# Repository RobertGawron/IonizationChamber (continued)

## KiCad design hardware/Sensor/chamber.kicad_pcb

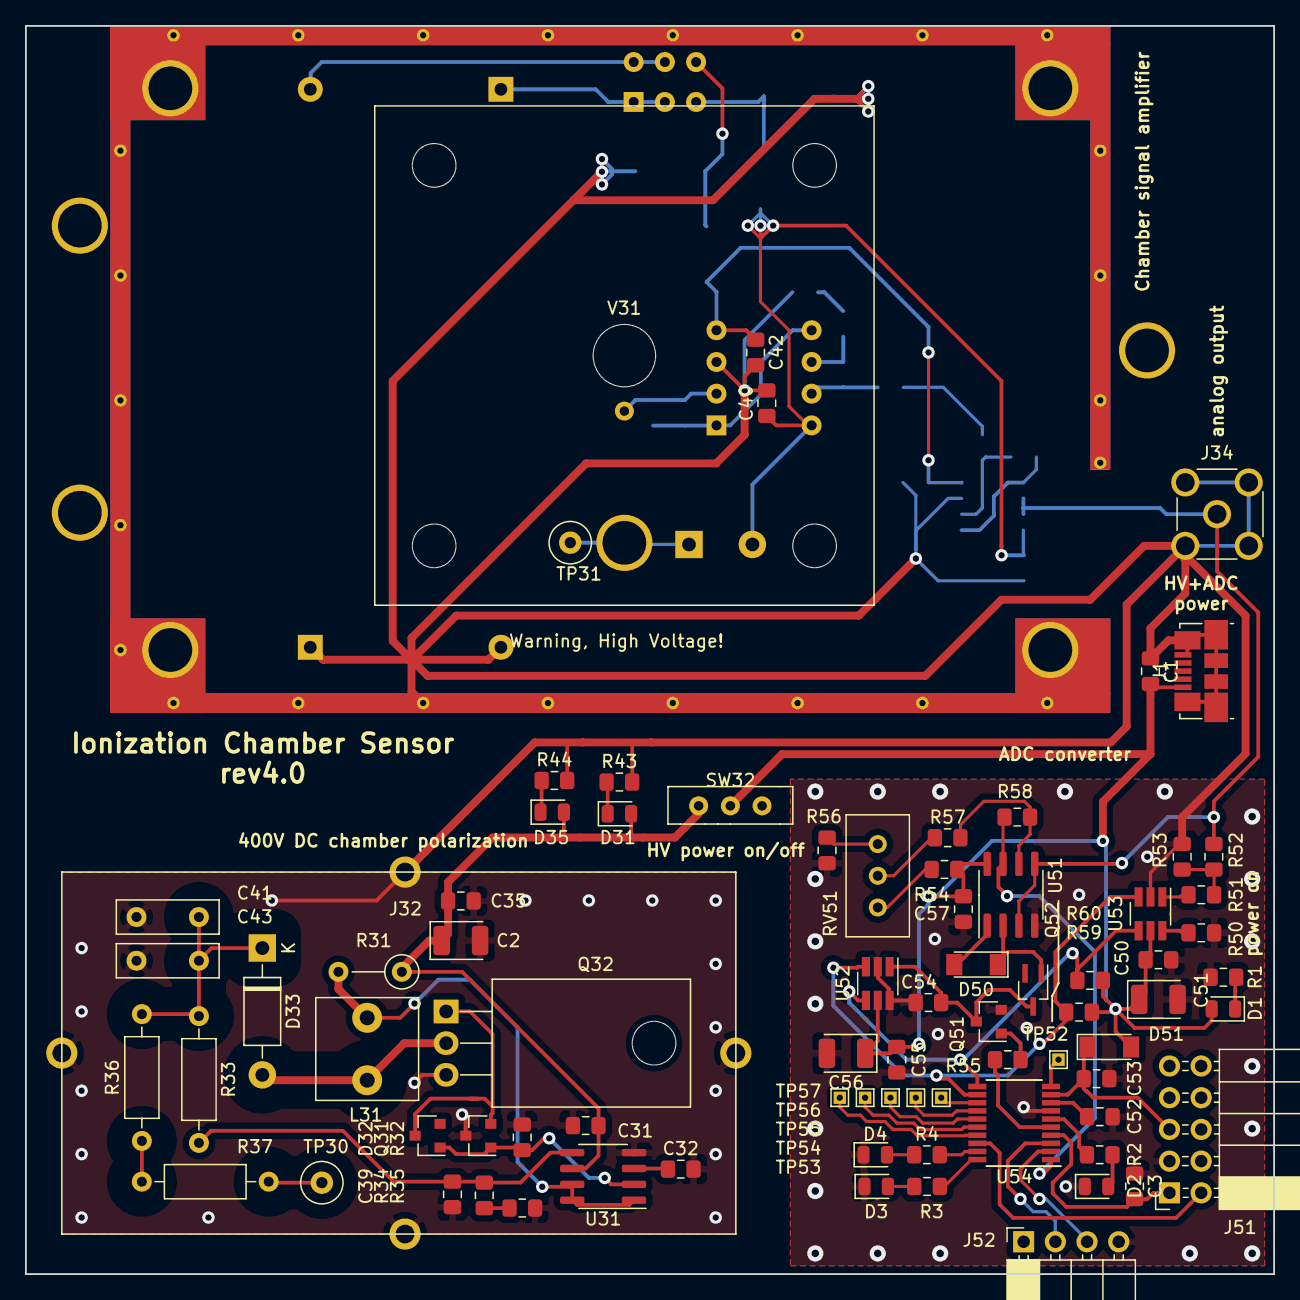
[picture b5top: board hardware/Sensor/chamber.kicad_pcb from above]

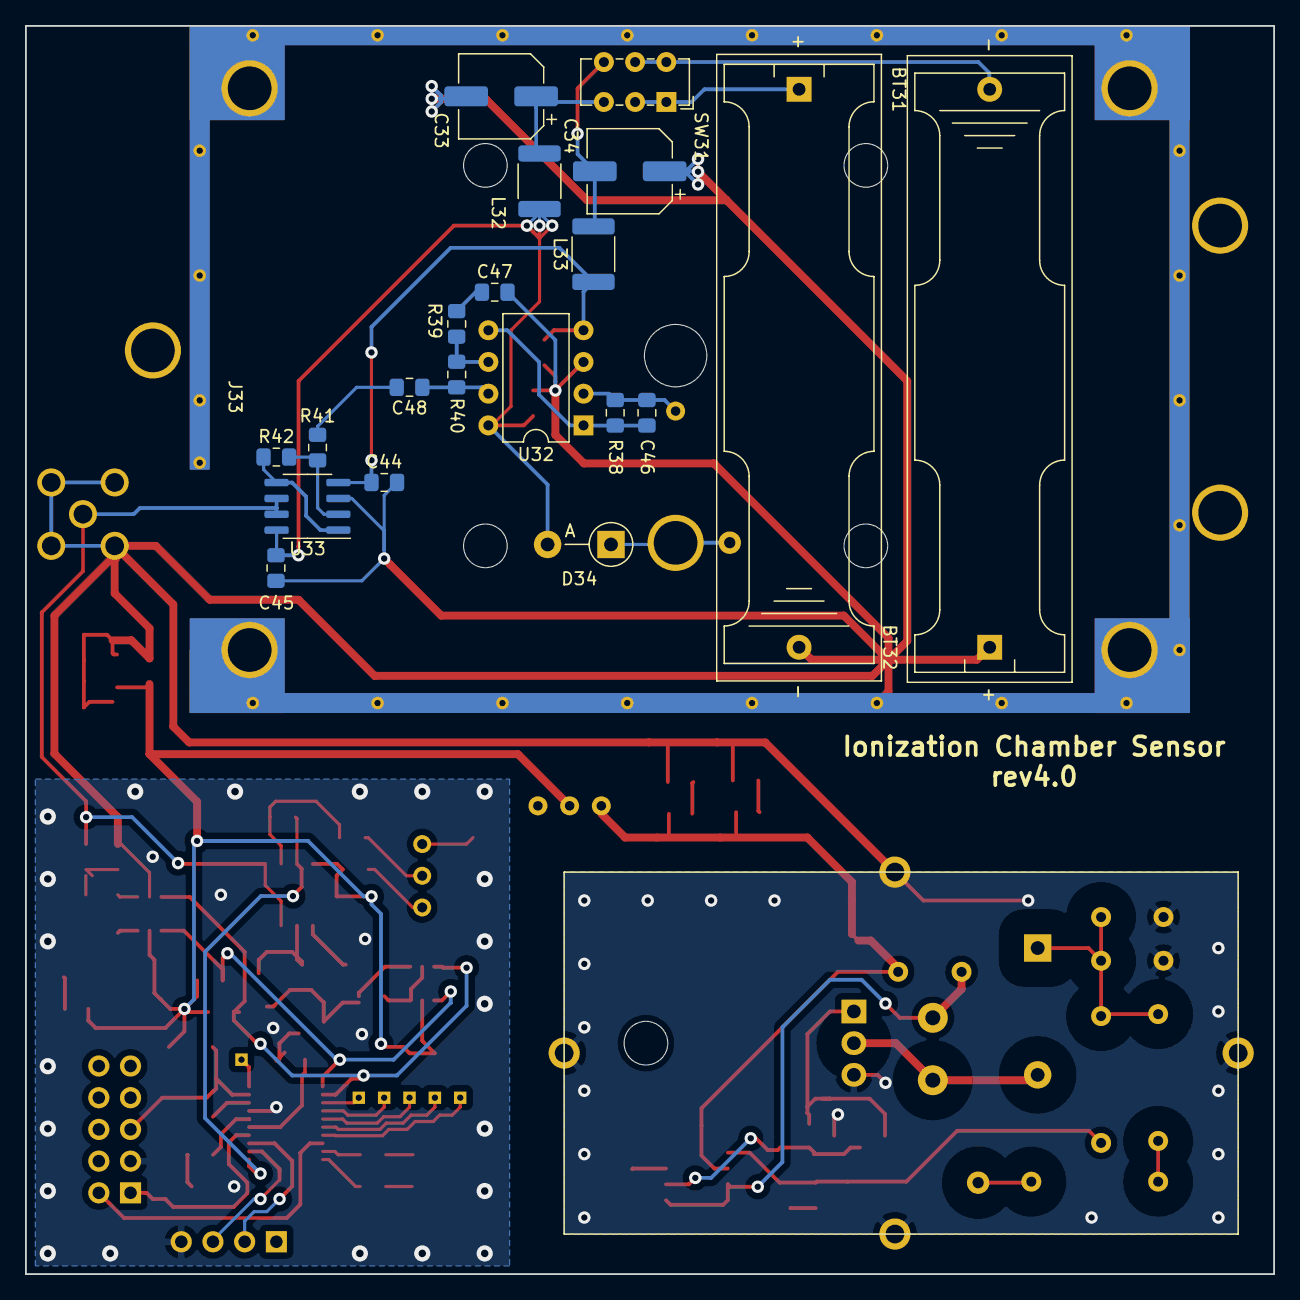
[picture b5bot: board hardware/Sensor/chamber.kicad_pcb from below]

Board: 2 copper layers, 100.0 x 100.0 mm, 100 parts (21 on the bottom side), 65 nets.

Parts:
BT31, BT32: 2 x 3V6; BatteryHolder_Keystone_2466_1xAAA
C1, C31, C35, C40, C42, C44, C45, C50, C52, C53, C54, C55, C57: 100n; C_0805_2012Metric_Pad1.15x1.40mm_HandSolder
C2: 100u/6V3; CP_EIA-3528-21_Kemet-B
C3, C39: 10n; C_0805_2012Metric_Pad1.15x1.40mm_HandSolder
C32: 3n3; C_0805_2012Metric_Pad1.15x1.40mm_HandSolder
C33, C34: 100u/16V; CP_Elec_6.3x5.4
C41, C43: 10n/600V; C_Disc_D8.0mm_W2.5mm_P5.00mm
C46: not mounted; C_0805_2012Metric_Pad1.15x1.40mm_HandSolder
C47, C48: 0R resistor; C_0805_2012Metric_Pad1.15x1.40mm_HandSolder
C51, C56: 10u; CP_EIA-3528-21_Kemet-B
D1, D31, D35: red; LED_0805_2012Metric
D2, D3, D4: LED; LED_0805_2012Metric
D32: D_Schottky; D_SOT-23_ANK
D33: 1N4007; D_DO-41_SOD81_P10.16mm_Horizontal
D34: 1N4007; D_DO-41_SOD81_P5.08mm_Vertical_AnodeUp
D50, D51: 1n148; D_MiniMELF
J1: USB_B_Micro; USB_Micro-B_Molex_47346-0001
J32: RF_Shield_Two_Pieces; IonizationChamberHVShield
J33: RF_Shield_Two_Pieces; IonizationChamberShield
J34: Conn_Coaxial; SMA_Molex_73251-2200_Horizontal
J51: Conn_02x05_Counter_Clockwise; PinSocket_2x05_P2.54mm_Horizontal
J52: Conn_01x04; PinSocket_1x04_P2.54mm_Horizontal
L31: 680m; L_Radial_L8.0mm_W8.0mm_P5.00mm_Neosid_NE-CPB-07E
L32, L33: u68; L_1812_4532Metric_Pad1.30x3.40mm_HandSolder
Q31: BC859; SOT-23
Q32: Q_NMOS_GDS; TO-220-3_Horizontal_TabDown
Q51: 2N7002; SOT-23
Q52: Q_NPN_BEC; SOT-323_SC-70_Handsoldering
R1, R43, R44: 520R; R_0805_2012Metric_Pad1.15x1.40mm_HandSolder
R2, R3, R4: 510R; R_0805_2012Metric_Pad1.15x1.40mm_HandSolder
R31: R22/0.5W; R_Axial_DIN0207_L6.3mm_D2.5mm_P5.08mm_Vertical
R32, R39, R41: 10k; R_0805_2012Metric_Pad1.15x1.40mm_HandSolder
R33, R36, R37: 10M; R_Axial_DIN0207_L6.3mm_D2.5mm_P10.16mm_Horizontal
R34, R54, R55, R56, R57, R58: 1k; R_0805_2012Metric_Pad1.15x1.40mm_HandSolder
R35: 30k; R_0805_2012Metric_Pad1.15x1.40mm_HandSolder
R38: 2*50G; R_0805_2012Metric_Pad1.15x1.40mm_HandSolder
R40: 120k; R_0805_2012Metric_Pad1.15x1.40mm_HandSolder
R42, R52: 22k; R_0805_2012Metric_Pad1.15x1.40mm_HandSolder
R50, R51: 0R; R_0805_2012Metric_Pad1.15x1.40mm_HandSolder
R53: R; R_0805_2012Metric_Pad1.15x1.40mm_HandSolder
R59, R60: 2k2; R_0805_2012Metric_Pad1.15x1.40mm_HandSolder
RV51: R_POT_TRIM; Potentiometer_Bourns_3296W_Vertical
SW31: SW_DPDT_x2; SW_E-Switch_EG1271_DPDT
SW32: SW_DPDT_x2; SwitchButtonGeneric
TP30, TP31: TestPoint; TestPoint_Loop_D2.60mm_Drill0.9mm_Beaded
TP52, TP53, TP54, TP55, TP56, TP57: TestPoint; TestPoint_THTPad_1.0x1.0mm_Drill0.5mm
U31: MC34063AD; SOIC-8_3.9x4.9mm_P1.27mm
U32: LMC662; DIP-8_W7.62mm
U33: LM358; SOIC-8_3.9x4.9mm_P1.27mm
U51: Opamp_Dual_Generic; SOIC-8_3.9x4.9mm_P1.27mm
U52, U53: MCP3425A0T-ECH; SOT-23-6_Handsoldering
U54: STM8S003F3P; TSSOP-20_4.4x6.5mm_P0.65mm
V31: Nuclear-Radiation_Detector; IonizationChamberSensor

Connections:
+BATT: C40.1, C45.1, D34.2, L32.1, U32.8, U33.8
-BATT: C42.1, C44.1, L33.1, U32.4, U33.4
/DataAcquisition/INT0: R58.2, U51.7, U54.1
/DataAcquisition/RST: C3.2, J51.1, U54.4
/DataAcquisition/RST_PEAK: R55.1, U54.5
/DataAcquisition/RX: J52.2, U54.3
/DataAcquisition/SCL: R59.1, U52.3, U53.3, U54.12
/DataAcquisition/SDA: R60.1, U52.4, U53.4, U54.11
/DataAcquisition/SWIM: J51.2, U54.18
/DataAcquisition/TX: J52.3, U54.2
/DataAcquisition/VCC_PROG: C53.2, D51.1, J51.5, U54.9
GND: BT31.2, BT32.1, C1.1, C2.2, C3.1, C31.1, C32.2, C33.2, C34.1, C35.2, C39.2, C40.2, C41.2, C42.2, C43.2, C44.2, C45.2, C47.2, C50.1, C51.2, C52.1, C53.1, C54.1, C55.1, C56.2, C57.1, D2.1, D3.1, D4.1, J1.5, J1.6, J32.1, J33.1, J34.2, J51.3, J52.4, Q31.3, Q32.3, Q51.2, R1.2, R32.2, R35.2, R43.2, R44.2, R50.2, R53.1, R56.2, U31.4, U32.3, U33.3, U51.4, U52.2, U52.6, U53.2, U54.7
unnamed: BT31.1, SW31.1, SW31.2
unnamed: BT32.2, SW31.4, SW31.5
unnamed: C2.1, C31.2, C35.1, D31.2, D35.2, R31.1, SW32.1, U31.6
unnamed: C32.1, U31.3
unnamed: C33.1, L32.2, SW31.3
unnamed: C34.2, L33.2, SW31.6
unnamed: C39.1, R33.2, R34.1, U31.5
unnamed: C41.1, C43.1, D33.1, R33.1, R36.2
unnamed: C46.1, R38.1, U32.1, U32.5
unnamed: C46.2, R38.2, U32.2, V31.2
unnamed: C47.1, R39.2
unnamed: C48.1, R40.1, U32.7
unnamed: C48.2, R41.2
unnamed: C52.2, U54.8
unnamed: C54.2, Q51.3, Q52.3, U52.1
unnamed: D1.1, R1.1
unnamed: D2.2, R2.1
unnamed: D3.2, R3.1
unnamed: D4.2, R4.1
unnamed: D31.1, R43.1
unnamed: D32.1, Q31.2, Q32.1
unnamed: D32.2, Q31.1, R32.1, U31.2
unnamed: D33.2, L31.2, Q32.2
unnamed: D34.1, TP31.1, V31.1
unnamed: D35.1, R44.1
unnamed: D50.1, Q52.1, U51.2
unnamed: D50.2, U51.1
unnamed: L31.1, R31.2, U31.1, U31.7, U31.8
unnamed: Q51.1, R55.2
unnamed: R2.2, U54.6
unnamed: R3.2, U54.20
unnamed: R4.2, U54.19
unnamed: R34.2, R35.1
unnamed: R36.1, R37.2
unnamed: R37.1, TP30.1
unnamed: R39.1, R40.2, U32.6
unnamed: R41.1, R42.2, U33.2
unnamed: R42.1, U33.1, U33.5
unnamed: R50.1, U53.6
unnamed: R51.1, U53.1
unnamed: R51.2, R52.1, R53.2
unnamed: R54.2, RV51.1
unnamed: R56.1, RV51.3
unnamed: R57.1, RV51.2
unnamed: R57.2, R58.1, U51.6
unnamed: TP52.1, U54.10
unnamed: TP53.1, U54.13
unnamed: TP54.1, U54.14
unnamed: TP55.1, U54.15
unnamed: TP56.1, U54.16
unnamed: TP57.1, U54.17
VCC_5V: C1.2, C50.2, C51.1, C55.2, C56.1, C57.2, D1.2, D51.2, J1.1, R54.1, R59.2, R60.2, SW32.2, U51.8, U52.5, U53.5
analog_output: J34.1, R52.2, U33.6, U33.7, U51.3, U51.5

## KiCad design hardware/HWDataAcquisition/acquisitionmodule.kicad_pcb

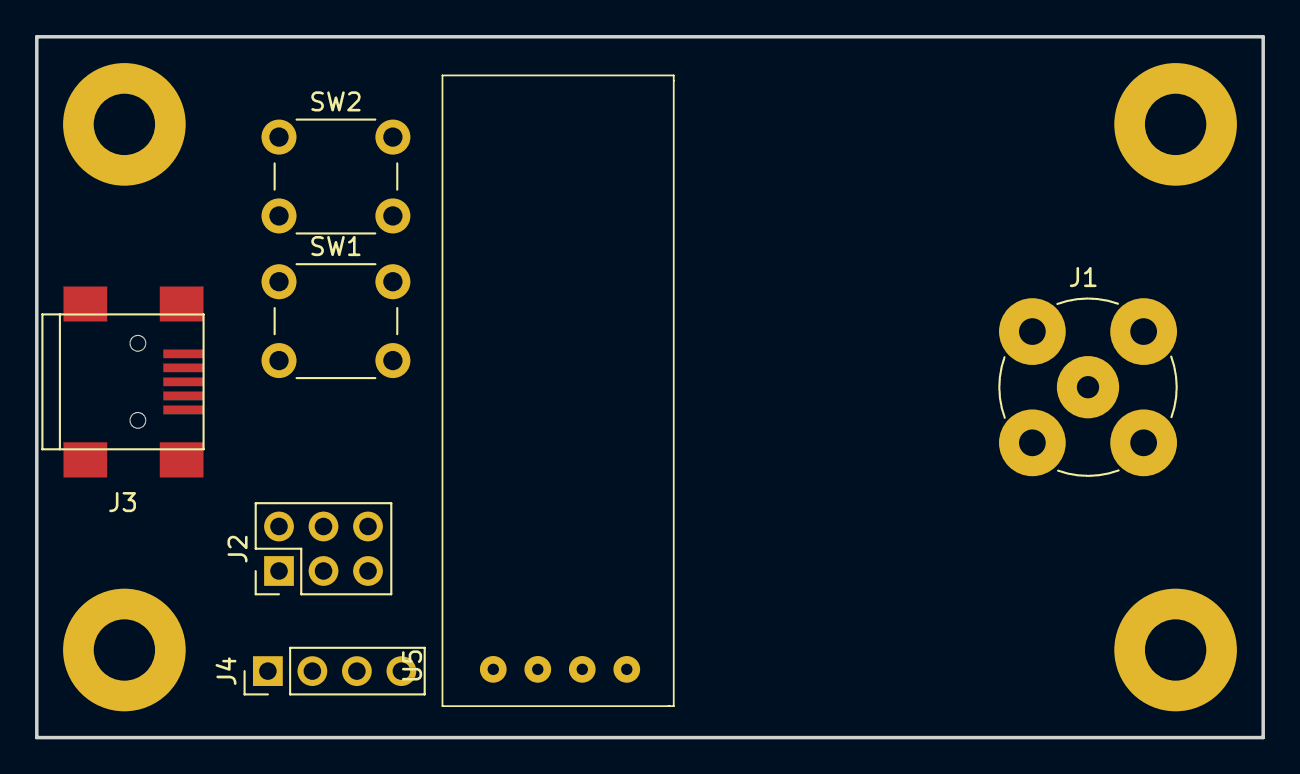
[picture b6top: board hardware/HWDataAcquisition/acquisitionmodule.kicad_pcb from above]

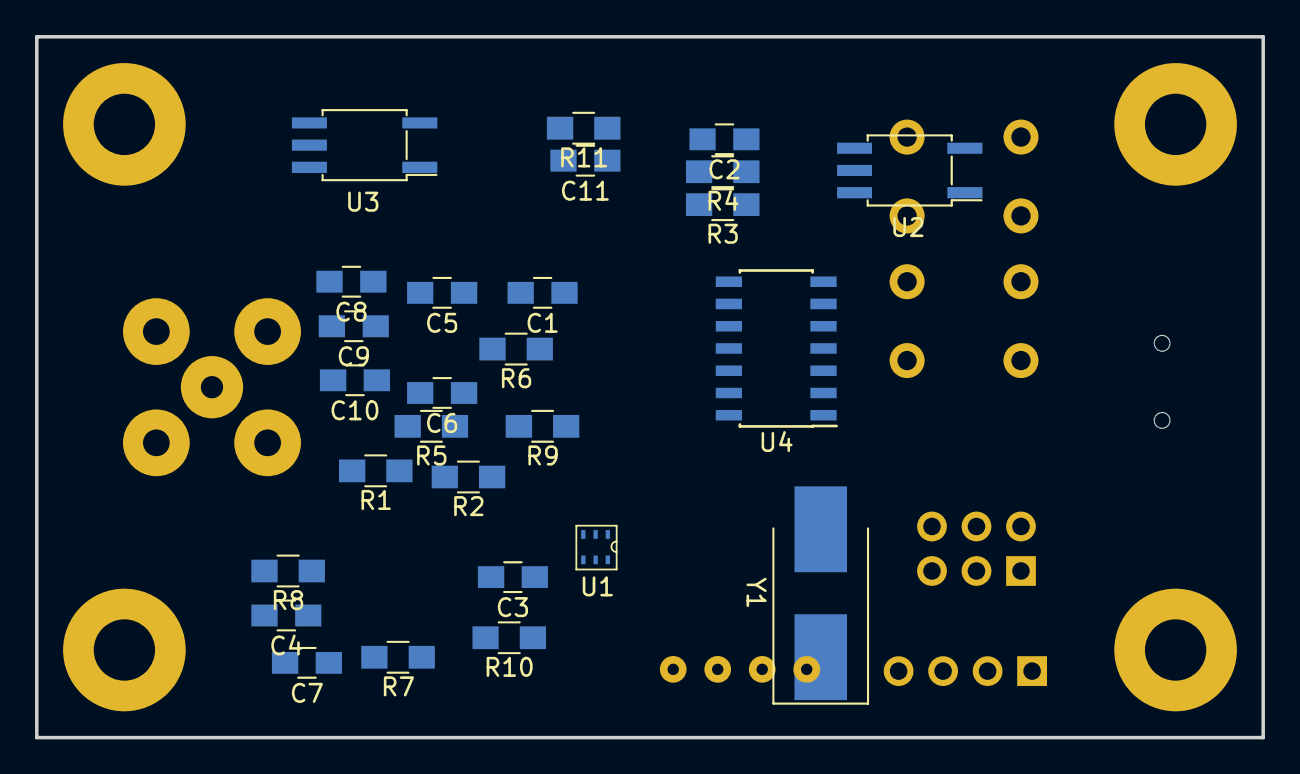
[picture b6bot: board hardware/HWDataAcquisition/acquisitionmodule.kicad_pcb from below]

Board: 2 copper layers, 70.0 x 40.0 mm, 34 parts (27 on the bottom side), 23 nets, no tracks yet.

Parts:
C1, C2, C3, C5, C10: C; C_0805_HandSoldering
C4, C6, C7, C8, C9, C11: 100n; C_0805_HandSoldering
J1: Conn_Coaxial; bnc-ci
J2: AVR-ISP-6; Pin_Header_Straight_2x03_Pitch2.54mm
J3: USB_B_Mini; USB_Mini-B
J4: Conn_01x04; Pin_Header_Straight_1x04_Pitch2.54mm
R1, R2, R3, R4, R5, R6, R11: R; R_0805_HandSoldering
R7, R8, R9, R10: 1k; R_0805_HandSoldering
SW1, SW2: SW_Push; SW_PUSH_6mm_h4.3mm
U1: ADS1110
U2, U3: TLV70033; SO-5_4.4x3.6mm_Pitch1.27mm
U4: ATtiny84A-SSU; SOIC-14_3.9x8.7mm_Pitch1.27mm
U5: 128x32px_LCD_I2C
Y1: Crystal; Crystal_SMD_7050-2pin_7.0x5.0mm_HandSoldering

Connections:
+3V3: C4.1, J2.2, J4.1, R7.1, R9.1, U3.5, U4.1, U5.1
/IO1: J4.3, U4.6
/IO2: J4.4, U4.5
/KEY_A: C9.1, R10.1, U4.11
/KEY_B: C8.1, R8.1, U4.10
/MISO: J2.1, U4.8
/MOSI: J2.4, U1.4, U4.7, U5.3
/RST: J2.5, U4.4
/SCK: J2.3, U1.3, U4.9, U5.4
/XTAL1: C6.1, U4.2, Y1.1
/XTAL2: C11.1, U4.3, Y1.2
GND: C1.2, C2.2, C3.2, C4.2, C5.2, C6.2, C7.2, C8.2, C9.2, C11.2, J1.2, J2.6, J3.4, J3.5, J3.6, J4.2, R1.2, R4.2, SW1.1, SW2.1, U1.2, U4.14, U5.2
unnamed: C1.1, C10.1, R2.1, U1.1
unnamed: C2.1, C5.1, R3.1, U1.5, U2.5
unnamed: C3.1, C7.1, J3.1, R5.1, U2.1, U2.3, U3.1, U3.3
unnamed: C10.2, J1.1, R1.1, R2.2
unnamed: J3.2, R5.2, R11.2
unnamed: J3.3, R6.2
unnamed: R3.2, R4.1, U1.6
unnamed: R6.1, U4.13
unnamed: R7.2, R8.2, SW1.2
unnamed: R9.2, R10.2, SW2.2
unnamed: R11.1, U4.12

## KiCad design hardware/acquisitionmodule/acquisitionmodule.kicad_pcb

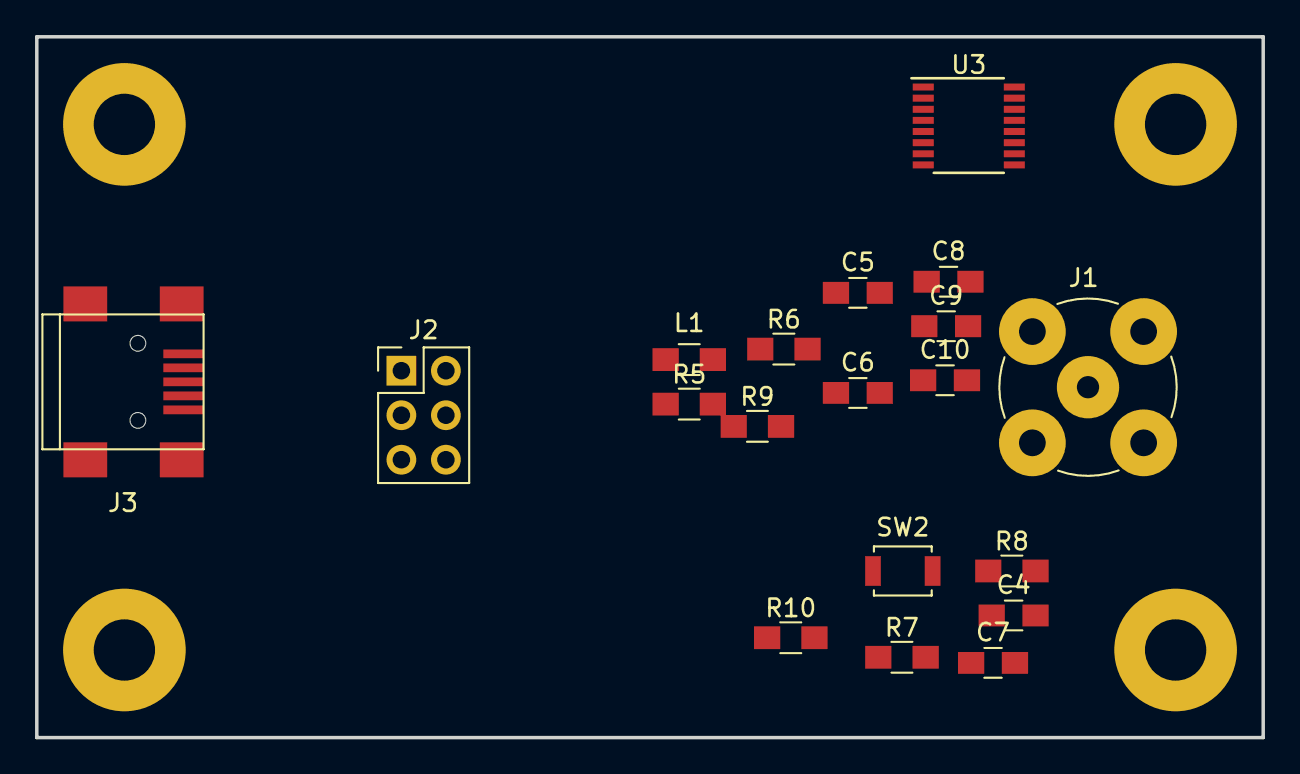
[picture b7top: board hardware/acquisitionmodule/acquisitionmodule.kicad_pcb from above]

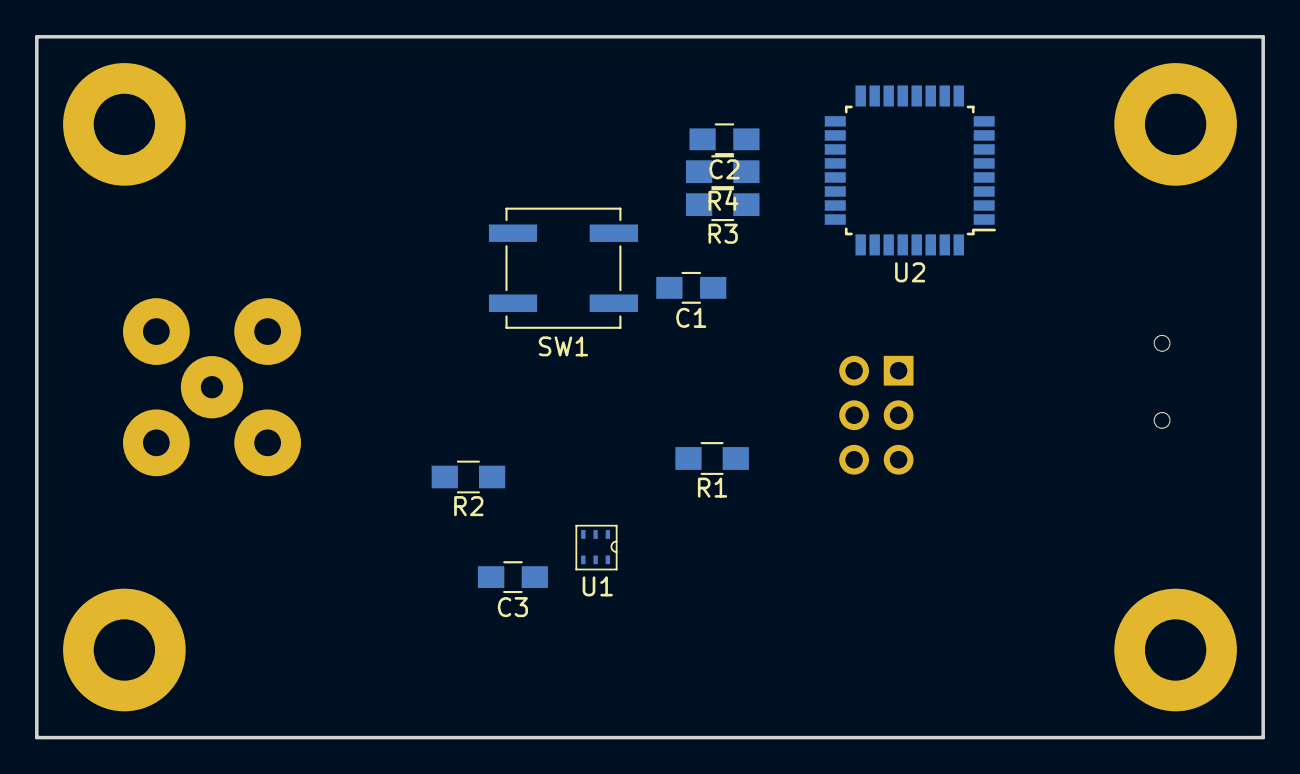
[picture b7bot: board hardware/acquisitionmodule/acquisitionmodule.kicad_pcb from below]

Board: 2 copper layers, 70.0 x 40.0 mm, 29 parts (10 on the bottom side), 21 nets, no tracks yet.

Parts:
C1, C2, C10: C; C_0805_HandSoldering
C3, C6, C7, C8, C9: 100n; C_0805_HandSoldering
C4, C5: 47p; C_0805_HandSoldering
J1: Conn_Coaxial; bnc-ci
J2: AVR-ISP-6; Pin_Header_Straight_2x03_Pitch2.54mm
J3: USB_B_Mini; USB_Mini-B
L1: L_Core_Ferrite; L_0805_HandSoldering
R1, R2, R3, R4: R; R_0805_HandSoldering
R5, R6: 22R; R_0805_HandSoldering
R7, R8, R9, R10: 1k; R_0805_HandSoldering
SW1: SW_Push; SW_SPST_B3SL-1022P
SW2: SW_Push; SW_SPST_B3U-1000P
U1: ADS1110
U2: ATtiny88-AU; LQFP-32_7x7mm_Pitch0.8mm
U3: FT201XS; SSOP-16_3.9x4.9mm_Pitch0.635mm

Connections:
/SCL: U2.28, U3.2
/SDA: U1.4, U2.27, U3.4
GND: C1.2, C2.2, C3.2, C4.2, C5.2, C6.2, C7.2, C8.2, C9.2, J1.2, J2.6, J3.4, J3.5, J3.6, R1.2, R4.2, SW1.1, SW2.1, U1.2, U2.5, U2.21, U3.5, U3.13
unnamed: C1.1, R2.1, U1.1
unnamed: C4.1, J3.2, R5.2
unnamed: C5.1, J3.3, R6.2
unnamed: C6.1, U3.3, U3.10, U3.11
unnamed: C7.1, J3.1, L1.1
unnamed: C8.1, R8.1
unnamed: C9.1, R10.1
unnamed: C10.2, J1.1, R1.1, R2.2
unnamed: J2.1, U2.16
unnamed: J2.3, U2.17
unnamed: J2.4, U2.15
unnamed: J2.5, U2.29
unnamed: R3.2, R4.1, U1.6
unnamed: R5.1, U3.9
unnamed: R6.1, U3.8
unnamed: R7.2, R8.2, SW1.2
unnamed: R9.2, R10.2, SW2.2
VCC: C2.1, C3.1, J2.2, L1.2, R3.1, R7.1, R9.1, U1.5, U2.4, U3.12

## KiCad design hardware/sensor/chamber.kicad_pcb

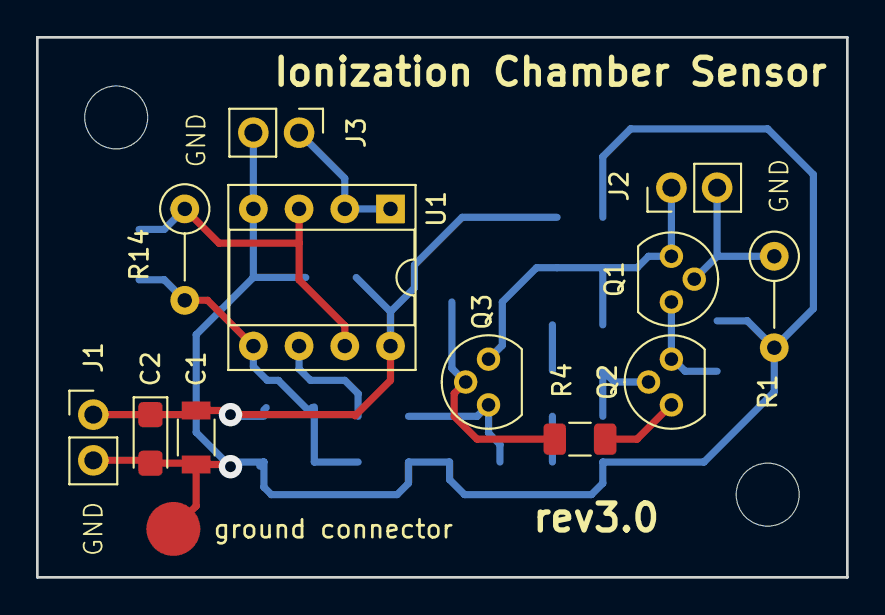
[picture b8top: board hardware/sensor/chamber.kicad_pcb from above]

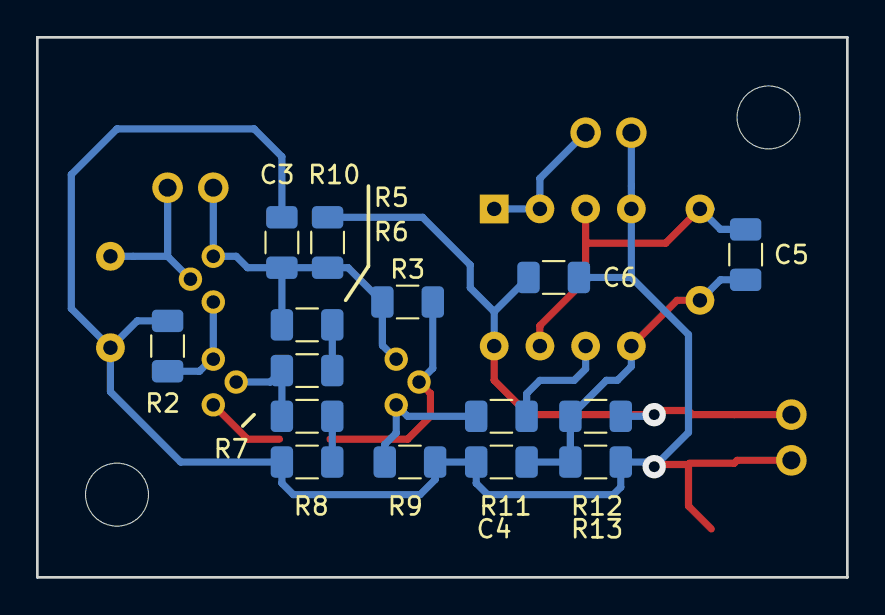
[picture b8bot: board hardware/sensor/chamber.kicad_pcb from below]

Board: 2 copper layers, 45.0 x 30.0 mm, 28 parts (15 on the bottom side), 15 nets.

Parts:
C1: 100n; C_1206
C2: 100u/16V; CP_EIA-3216-18_Kemet-A
C3, C5, C6: 100n; C_1206_3216Metric
C4: C; C_1206_3216Metric
J1: Power; PinHeader_1x02_P2.54mm_Vertical
J2: Chamber; PinHeader_1x02_P2.54mm_Vertical
J3: Output; PinHeader_1x02_P2.54mm_Vertical
Q1: Q_NJFET_DGS; TO-92
Q2: BC546; TO-92
Q3: BC327; TO-92
R1: 1G; R_Axial_DIN0207_L6.3mm_D2.5mm_P5.08mm_Vertical
R2, R4: 270k; R_1206_3216Metric
R3: 100k; R_1206_3216Metric
R5, R11: 47k; R_1206_3216Metric
R6, R7: 0R; R_1206_3216Metric
R8: 150k; R_1206_3216Metric
R9: 220k; R_1206_3216Metric
R10: 1k; R_1206_3216Metric
R12, R13: R; R_1206_3216Metric
R14: 4M7; R_Axial_DIN0207_L6.3mm_D2.5mm_P5.08mm_Vertical
U1: LMC6082; DIP-8_W7.62mm_Socket
ground connector: Measurement_Point_Round-SMD-Pad_Big

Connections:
GND: C1.2, C2.2, C3.2, C4.2, C6.2, J1.2, J3.2, R1.2, R2.2, R8.2, R9.2, R13.2, U1.4, ground connector.1
unnamed: C1.1, C2.1, C6.1, J1.1, R10.2, R12.1, U1.8
unnamed: C3.1, J2.1, Q1.1, Q3.3, R3.1, R5.1, R10.1
unnamed: C4.1, C5.2, R12.2, R13.1, R14.2, U1.5
unnamed: C5.1, R14.1, U1.3, U1.7
unnamed: J2.2, Q1.2, R1.1
unnamed: J3.1, U1.1, U1.2
unnamed: Q1.3, Q2.3, R2.1
unnamed: Q2.1, R4.2
unnamed: Q2.2, R6.2, R7.1
unnamed: Q3.1, R9.1, R11.2
unnamed: Q3.2, R3.2, R4.1
unnamed: R5.2, R6.1
unnamed: R7.2, R8.1
unnamed: R11.1, U1.6

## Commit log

2018-09-19 version before sending to factory
2018-09-19 Create LICENSE
2018-09-21 directory structure change
2018-09-21 dummy draft
2018-09-21 local footprint lib
2018-09-21 ADS1110 footprint
2018-09-21 old footprint removed
2018-09-21 changes in prive libs
2018-09-22 tlv700 footprint added
2018-09-22 button connection fix
2018-09-22 almost done schemat
2018-09-22 fixed diagram placement
2018-09-22 pin properties fix
2018-09-22 drc free schemat
2018-09-22 project structure change
2018-09-22 added missing file
2018-09-22 change project structure
2018-09-22 directory change
2018-09-22 empty sw solution
2018-09-22 empty classes for various stuff
2018-09-22 vusb lib added
2018-09-22 vusb is now part of the project
2018-09-22 removed vs local file
2018-09-22 added i2c lib
2018-09-22 fixed compilation error
2018-09-22 files rename
2018-09-23 added symbol for attiny (with pinouts)
2018-09-23 change settings to use c++11
2018-09-23 chemat is now more redable
2018-09-25 fixed class names
2018-09-25 iapp builder added
2018-09-25 fixed filename after class name changes
2018-09-25 dummy init method for drivers
2018-09-25 finally found some good looking i2c lib
2018-09-25 passing i2c object in ctors
2018-09-26 adapter for i2c lib
2018-09-26 minor layout adjustments
2018-09-26 driver usb is now driver uart
2018-09-26 fixed file names
2018-09-26 removed boilerplate code
2018-09-26 adc initialization
2018-09-26 data acquisition routine
2018-09-26 whitespace cleanup
2018-09-26 bit ids fix
2018-09-26 define name fix
2018-09-26 draft of interrupt registration
2018-09-27 draft of the script
2018-09-27 folder structure change
2019-02-16 added ltspice simulation
2019-02-16 fixes after hw tests
2019-02-21 simulation of the chamber electric field
2019-02-21 removed junk files
2019-02-21 fixed simulation folder structure
2019-02-21 remove junk files
2019-02-22 usable version
2019-05-05 draft of transimpedance opamp usage
2019-05-12 fixed footprints
2019-05-12 generic symbol for sensor used
2019-05-12 hw converter added
2019-05-18 sensor + high voltage schemat
2019-05-18 changed power source
2019-05-18 draft of digital part
2019-05-18 added footprints
2019-05-18 draft of element placement
2019-05-19 grouped elements and grounds
2019-05-19 fixed chasis for sensor
2019-05-19 improved vcc and ground routing
2019-05-19 tarted routing first tage amplifier
2019-05-23 minor fixes
2019-05-23 layout for hv generator
2019-05-23 draft of adc converter
2019-05-25 further routing
2019-05-25 further routing of digital part
2019-05-25 ground between masses
2019-05-25 befor board flip
2019-05-25 dirty version of adc routing
2019-05-25 ruting amplifier part
2019-05-25 befoure routing amp gnd
2019-05-25 all done for raw version
2019-05-26 ready to sent to manufacture
2019-05-26 added pic for readme
2019-06-02 deleted topor files, added footprint
2019-06-04 draft of firmware project structure
2019-06-04 makefile added
2019-06-04 remove junk file
2019-06-08 template to setup project
2019-06-08 added buuld configurations
2019-06-15 draft that can be compiled
2019-06-15 don't rebuild everything on change
2019-06-15 added app builder and peak detector
2019-06-15 headers with common stuff added
2019-06-15 added error prgama to avoid bool redefinition
2019-06-15 added peak detector initialization
2019-06-15 initial sw version
2019-06-15 pcb ready to send to factory
2019-06-15 draft of firmware
2019-06-15 revision 4.0
2019-06-15 added readme content
2019-06-15 revision 4.0 (reworked git history)
2019-06-16 added datalogger module, changed cpu id, added led
2019-06-29 raw setup on eclipse and raspberry
2019-06-30 Fixes after moving to target board
2019-06-30 Added GUI module
2019-06-30 draft of communication via LEDs
2019-07-02 draft of uart tx implementation
2019-07-03 rename modules
2019-07-03 uart used as printf output
2019-07-04 awu not working due to binary size
2019-07-06 minor cleanup
2019-07-06 crude timer implementation
2019-07-06 remove magic numbers
2019-07-06 cleanup in sensors part
2019-07-06 further cleanup
2019-07-08 cleanup
2019-07-13 cleanup in initializers
2019-07-13 Redundant mkdir step in makefile #73
2019-07-13 added first image of the board
2019-07-13 fix #63
2019-07-13 code size reduction to fit i2c
2019-07-14 minor changes to not working i2c stuff
2019-07-14 fix #56 #74
2019-07-14 fix #59 #71
2019-07-20 private methods made as static
2019-07-20 This closes #84
2019-07-20 further digging into i2c
2019-07-20 updated docs for actual pcb version
2019-07-21 fixes #83
2019-07-27 fixes #86
2019-07-27 code formated using uncrustify
2019-07-28 related to #91 able to select adress (visible on scope)
2019-07-28 sending dummy data
2019-07-28 formated it a bit
2019-07-28 working reading/writing via i2c
2019-07-28 draft of buisness logic to handle meassurements
2019-07-28 further implementation of buisness logic
2019-07-28 logging semi-dummy adc readings to uart
2019-07-28 variant with and without printf
2019-07-28 directory structure update
2019-07-28 logging data via uart improved
2019-07-28 further implementation of i2c communication
2019-08-03 working i2c read/write
2019-08-03 i2c read is ok on ociloscope not on firmware
2019-08-03 i2c read works kind of on firmware too
2019-08-03 formatting improved
2019-08-03 improved formatting
2019-08-04 minor code cleanup
2019-08-04 libs folder structure simplification
2019-08-04 updated device photo
2019-08-04 update of measurement data type
2019-08-04 bit operations moved to a spearate file
2019-08-04 dummy reading of firmware meassurements
2019-08-04 continous meassurement
2019-08-04 removed magic numbers
2019-08-04 adc logic moved to separate script
2019-08-04 minor formatting changes
2019-08-04 i2c works, this time for real
2019-08-04 more recent photo
2019-08-04 fix in communication pc vs device
2019-08-04 remove unneded code
2019-08-05 architecture documents added
2019-08-05 protocol for uart communication
2019-08-05 fixed uart protocol implementation and usage
2019-08-05 diagrams generated
2019-08-05 make diagram more redable
2019-08-05 improved diagram
2019-08-06 typo fixes
2019-08-06 cmake config
2019-08-07 detailed readme
2019-08-07 able to start compilation, faill on passing defines
2019-08-09 travis build for r and latex part
2019-08-09 add missing travis config
2019-08-09 added ci status
2019-08-09 fixed type
2019-08-09 fixed typo (again)
2019-08-10 trying to compile lib
2019-08-10 sdcc build
2019-08-10 fixed sdcc build
2019-08-10 platform related defines hardcoded
2019-08-10 able to fail compilation of files
2019-08-10 dummy compilation ok, but link fail
2019-08-10 working cmake
2019-08-10 added flashing device after build
2019-08-10 downgrade to c95
2019-08-10 fixes after review
2019-08-10 use cmake
2019-08-10 fix #148
2019-08-11 fix #157
2019-08-11 fix #156
2019-08-11 fix #154
2019-08-11 fix #161
2019-08-11 fix #152
2019-08-11 added host architecture
2019-08-11 host architecture picture added
2019-08-11 chapter name changed
2019-08-12 fix #181
2019-08-13 fix #124, build will fail due to errors found
2019-08-13 fix #124 (added installing of cppcheck)
2019-08-13 fix #149
2019-08-13 fix #149 (indentation fix)
2019-08-15 fix #159
2019-08-15 fix #159 #158 #147 #145
2019-08-16 fix #198
2019-08-16 fix #203
2019-08-16 fix #202
2019-08-16 fix #194
2019-08-16 fix #186
2019-08-16 fix #196
2019-08-16 remove cppcheck error (#192)
2019-08-16 fix #64
2019-08-16 fix #197
2019-08-16 fix #192
2019-08-16 paritial #210
2019-08-16 fixed path to python scripts
2019-08-19 boxplot to analyze results between samples
2019-08-19 correct file extension
2019-08-19 remove useless file
2019-08-20 fix #216
2019-08-25 fix #218
2019-08-26 fix #210
2019-08-26 fix #224
2019-08-26 fix #223
2019-08-26 fix #184
2019-09-03 not mounted parts marked on diagram
2019-09-03 fix #211
2019-09-07 aplied missing changes after hw assembly
2020-05-30 added picture of the device to README.md
2020-10-22 Unify folder name convention with my other repos (first upper letter singular nouns)
2020-10-22 remove pointless comments
2020-10-23 ci support for static code analysis
2020-10-23 ci support for building firmware
2020-10-24 local files added to .gitignore
2020-10-24 fix python's linter issues + improve docs
2020-10-24 move (for diagrams) from .png to .svg
2020-10-24 move (for diagrams) from .png to .svg - fix img path
2020-11-06 Fix grammar mistakes (found by Code Spell Checker add-on in VSCode). (fix #245)
2021-07-03 add draft of pcb with high voltage supply and opamp power supply
2021-07-04 finished design of the power power supply pcb
2021-07-04 draft of sensor pcb
2021-07-10 draft of routing of sensor
2021-07-17 switched from stm32 nucleo to stm8, added user interface, added draft of pcb routing
2021-07-18 finished pcb design
2021-07-22 fix #249
2021-07-24 added references to LCSC shop (for some components), slighty improved routing
2021-07-25 fix #249, fix #251
2021-08-07 fix #186 + add missing files
2021-08-07 fix #255, fix #256
2021-08-07 fix #230
2021-08-07 =fix #226
2021-08-07 fix #253
2021-08-07 cleanup in order to be able to do #260 and #127
2021-08-15 cleanup after transition to KiCad6
2024-08-17 this is what was send for pcb production
2024-12-10 design of hw rev 6.0
2024-12-11 draft
2024-12-11 impr structure
2024-12-11 xxxxxx
2024-12-11 use docker
2024-12-11 add more uml diagrams
2024-12-11 fix formatting
2025-06-23 cmake cleanup, add unit tests
2025-06-23 unit tests cleanup
2025-06-23 test
2025-06-26 debug
2025-06-26 start fucking over
2025-06-26 =NEW
2025-07-04 rework firmware, pc app, ci and docs
